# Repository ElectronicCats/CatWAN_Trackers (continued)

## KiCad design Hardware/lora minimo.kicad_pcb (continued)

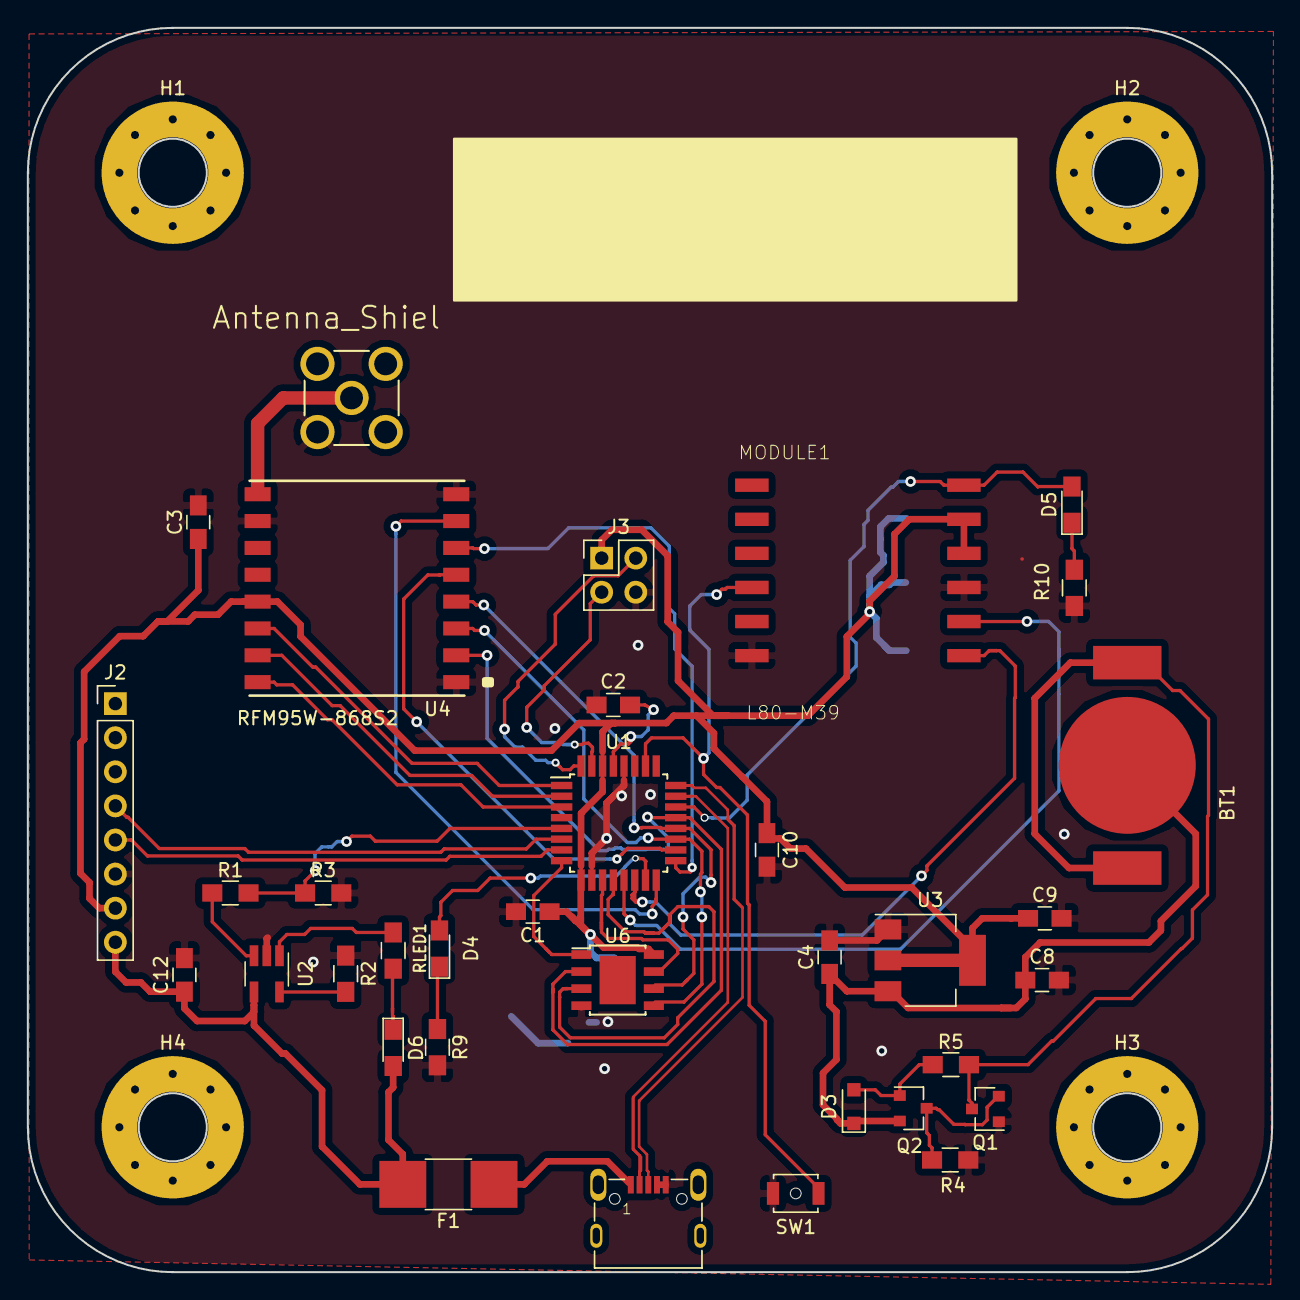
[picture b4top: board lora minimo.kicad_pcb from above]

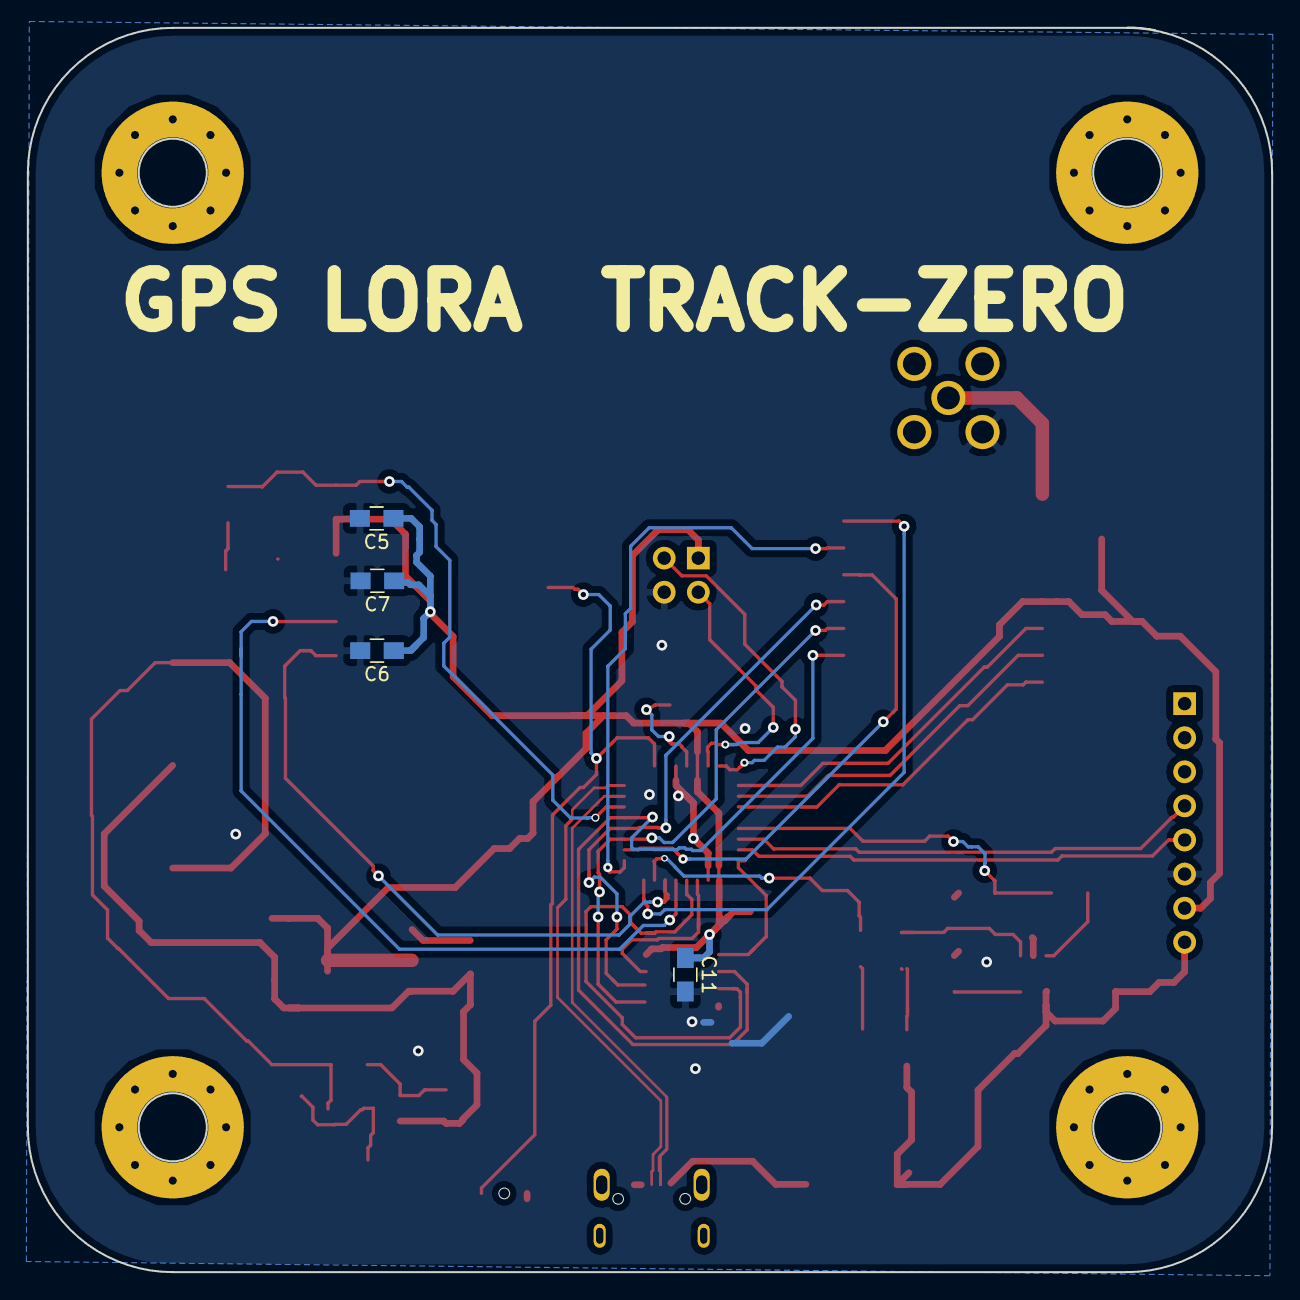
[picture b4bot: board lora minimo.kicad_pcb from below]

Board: 2 copper layers, 92.7 x 92.7 mm, 43 parts (4 on the bottom side), 40 nets.

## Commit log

2018-11-27 inicial schematic
2018-11-27 add gitignore
2018-11-27 add cache lib
2018-11-30 ACELEROMETER AND EPROOM
2018-12-07 MEMORY AND ACCELEROMETER UPDATE
    CHANGED BY A FLASH MEMORY OF 2 MB AND CHANGED BY ACCELEROMETER MODULE
2019-01-04 ADDED FOOTPRINTS
    ADDED FOOTPRINTS AND DID UPDATES
2019-01-04 update gitignore
2019-01-04 Move datasheets
2019-01-04 Add PCB and netlist
2019-01-04 connection update
2019-01-05 add netist and pcb
2019-01-31 PCB test
    pcb design and fingerprint reallocation
2019-03-23 add pcb gps vehicular and minimo
2019-03-26 remove files unnecesary
2019-03-26 add logos gps minimo
2019-03-26 add logos
2019-03-29 Round off the corners and change screen printing gps_vehicular
2019-03-29 Round off the corners and change screem printing gps_minimo
2019-03-29 add screen printing swd pins gps_vehicular
2019-11-05 rename paths and rename
2019-11-05 schematic add
